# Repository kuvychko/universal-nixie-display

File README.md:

# universal-nixie-display

A programmable desktop display: six IN-14 Nixie tubes in a row, one A101 dekatron, a 2.8" ESP32
touchscreen and a rotary encoder, in a matte PLA enclosure on a tilt base. It is meant to be an
enjoyable object on its own (clock, timer, demo) and a numeric output device for a computer,
Raspberry Pi or experiment, driven over USB serial with a small SCPI-style command set.

**Companion site:** [kuvychko.github.io/universal-nixie-display](https://kuvychko.github.io/universal-nixie-display/)
· **Interactive explainer:** [How a dekatron counts](https://kuvychko.github.io/universal-nixie-display/how-it-works/dekatron/)

## The dekatron on the bench

The first tube to run is the A101, on a bench fixture: a printed housing for its socket, a shroud
over the tube, and a white clamshell around a perf board with a resistor divider and two step
buttons ([bench test](docs/bringup.md#optional-a101-bench-test)). It strikes, holds its glow and
steps reliably in both directions; the video shows it stepping from a 400 V supply.

*The bench fixture running from a 400 V supply (2026-10-20), and a still from the
[video](https://youtube.com/shorts/yVVf5zhSL-M) of the tube stepping (2026-10-19).*

The socket housing and shroud are not just for the bench: they go into the finished display as
they are, with the dekatron held horizontally, its end facing the viewer. The M3 inserts in the
housing's side faces are its mounting points in the enclosure. Print files and hardware are in
[enclosure/](enclosure/README.md#dekatron-bench-test-a101-bench-test-fixture).

## The dekatron on its own board

On 2026-10-25 the A101 ran from the first assembled controller/PSU board: the board's own HV
converter, bias supplies and guide drivers, with the RP2040 stepping the glow and counting its
passes over the index cathode. The video shows a demo loop: glow held still, slow rotation both
ways, speeding up to 200 steps/s, and a back-and-forth swing
([`tools/dekatron_demo.py`](tools/dekatron_demo.py), on the
[bring-up firmware](firmware/dekatron-bringup/README.md)). Stepping runs of up to 200 steps/s
in both directions counted every index pass exactly. With the tube lit the converter first held
only about 415 V of its 451 V setpoint; noise at the current-sense pin was ending its cycles
early. Since 2026-10-26, after three small reworks with kit parts, it regulates at the setpoint
with the tube lit ([assembly log](characterization/dekatron/2026-10-24_assembly_log.md)).

*The first controller/PSU board driving the A101
([video](https://youtu.be/51U_WKXrzoA), 2026-10-25).*

## Status

**Phase 1D and Phase 2 in parallel.** The dekatron controller/PSU board 1 is assembled: its rails,
HV converter and tube drive pass bring-up steps 1-3 (some measurements deferred), and the A101
steps and indexes on it under the [bring-up firmware](firmware/dekatron-bringup/README.md). Its
step-rate limits are measured: clean to 4000 steps/s, four times the datasheet rate, with counts
lost at 5000 ([logs](characterization/dekatron/2026-11-12_speed_sweep.md),
[2026-11-15](characterization/dekatron/2026-11-15_speed_sweep.md)). The
[dekatron controller firmware](firmware/dekatron/README.md) runs the tube over its USB
console, including the periodic index check and skip recovery
([log](characterization/dekatron/2026-11-14_index_check.md)), and ran an hour at its 2000 steps/s
limit, about 7.1 million steps, without a count error
([soak](characterization/dekatron/2026-11-15_overlap_soak.md)); its I2C path and the remaining
step 4-5 tests are next. The Nixie board is designed: schematics, PCB,
fab outputs and an [assembly checklist](hardware/nixie/assembly.md) are done; its parts were
ordered on 2026-11-10 and the board from PCBWay on 2026-11-11. The purchased Nixie HV module has
been measured on the bench ([log](characterization/nixie/2026-11-01_hv_module.md)). The planning
baseline is [docs/project_plan.md](docs/project_plan.md); design decisions and open items are in
[docs/hardware.md](docs/hardware.md), results in [docs/bringup.md](docs/bringup.md).

| Phase | Deliverable | State |
|---|---|---|
| 1A | Dekatron board architecture and power budget for 12 VDC input | Done |
| 1B | Hierarchical schematics and simulation evidence | Done (open simulation items in `docs/hardware.md`) |
| 1C | Dekatron controller/PSU PCB, BOM, fab files | Done: boards and parts received 2026-10-15/16 |
| 1D | Sectional bring-up and standalone firmware | **In progress:** board 1 hardware brought up (steps 1-3), step-rate limits measured (3a); controller firmware motion, index check and a one-hour soak tested with HV (step 4); I2C path and fault paths next |
| 2 | Nixie PSU qualification and six-tube controller/mount | **In progress:** HV module bench data and inrush; board designed; parts and boards ordered (2026-11-10/11) |
| 3 | ESP32 UI, encoder, I2C master, USB host commands | Not started |
| 4 | Enclosure | Started: A101 socket housing and shroud printed and in use |
| 5 | Rev A release | Not started |

### Dekatron controller/PSU at a glance

Readable without KiCad. Board as fabricated (commit f4fd414, ordered 2026-10-09); the schematic
title block still reads "Rev A draft". **Not yet fully validated:** bring-up is in progress
(Phase 1D); on board 1 the HV supply and tube drive run, the HV at its setpoint under load after
reworks to the current sense and switching frequency ([docs/bringup.md](docs/bringup.md)).

| What | File |
|---|---|
| Schematic (PDF, 4 sheets) | [hardware/dekatron/docs/dekatron-schematic.pdf](hardware/dekatron/docs/dekatron-schematic.pdf) |
| Board renders | [top](hardware/dekatron/docs/dekatron-pcb-top.png), [bottom](hardware/dekatron/docs/dekatron-pcb-bottom.png) |
| Bill of materials | [hardware/dekatron/bom.csv](hardware/dekatron/bom.csv) |
| Assembly checklist | [hardware/dekatron/assembly.md](hardware/dekatron/assembly.md) |
| Gerbers and drill files | [hardware/dekatron/fab/](hardware/dekatron/fab/README.md) |
| Bring-up results | [docs/bringup.md](docs/bringup.md) |

*Render and board 1 as assembled by hand (2026-10-27). The yellow disc capacitor beside U106 is a
bring-up rework: 470 pF at the converter's current-sense pin.*

### Nixie controller/mount at a glance

Six IN-14s, three HV5622 drivers and an RP2040 on one 164 x 53 mm board. Fabrication outputs
ordered from PCBWay 2026-11-11 (parts 2026-11-10); **not yet built**.

| What | File |
|---|---|
| Schematic (PDF, 3 sheets) | [hardware/nixie/docs/nixie-schematic.pdf](hardware/nixie/docs/nixie-schematic.pdf) |
| Board renders | [top](hardware/nixie/docs/nixie-pcb-top.png), [bottom](hardware/nixie/docs/nixie-pcb-bottom.png) |
| Bill of materials | [hardware/nixie/bom.csv](hardware/nixie/bom.csv) |
| Assembly checklist | [hardware/nixie/assembly.md](hardware/nixie/assembly.md) |
| Gerbers and drill files | [hardware/nixie/fab/](hardware/nixie/fab/README.md) |

## Architecture

```
 12 VDC adapter ──┬──────────────► purchased Nixie HV module (~170-180 V) ──► Nixie controller/mount
                  │                                                           (6× IN-14, 3× HV5622, RP2040-Zero)
                  └──► dekatron controller/PSU ──► A101 (HV, bias, guide drive, index sense, RP2040-Zero)
                         │ 5 V buck out
                         ▼
                   ESP32 2.8" display board ◄── USB-C to host (SCPI-style serial)
                   (UI, encoder, presets, I2C master)
                         │ I2C, 3.3 V
                         └──► dekatron controller, Nixie controller
```

The ESP32 owns *what* is displayed; the RP2040 controllers own time-sensitive sequences and
hardware state. See [docs/architecture.md](docs/architecture.md).

## Documentation

| Document | Contents |
|---|---|
| [docs/project_plan.md](docs/project_plan.md) | Planning baseline: scope, decisions, phases and acceptance gates |
| [docs/architecture.md](docs/architecture.md) | Power distribution, board boundaries, ownership |
| [docs/hardware.md](docs/hardware.md) | Electrical design, open decisions, harness tables |
| [docs/i2c_protocol.md](docs/i2c_protocol.md) | Versioned controller command/status contracts |
| [docs/host_interface.md](docs/host_interface.md) | USB serial / SCPI-style host contract |
| [docs/bringup.md](docs/bringup.md) | Module bring-up procedures and acceptance results |
| [docs/development.md](docs/development.md) | Toolchains, KiCad workflow, generated-file policy |
| [docs/references.md](docs/references.md) | Datasheets, source designs, attribution and reuse terms |
| [docs/companion_site.md](docs/companion_site.md) | Plan for the companion website (`website/`); the published site is [here](https://kuvychko.github.io/universal-nixie-display/) |

## Repository layout

| Path | Contents |
|---|---|
| `hardware/dekatron/` | Dekatron controller/PSU KiCad project; `simulation/` holds supply and drive/sense models |
| `hardware/nixie/` | Nixie controller/mount KiCad project (boards ordered 2026-11-11) |
| `hardware/power/` | Purchased Nixie PSU specification and system power harness (planned, Phase 2) |
| `hardware/lib/` | Shared symbols and footprints (planned; the dekatron board's own library is in `hardware/dekatron/lib/`) |
| `firmware/display/` | ESP32 main application, PlatformIO (planned, Phase 3) |
| `firmware/dekatron/` | RP2040 dekatron controller and standalone diagnostics: [spec and build](firmware/dekatron/README.md), v0.1 (Phase 1D) |
| `firmware/dekatron-bringup/` | Dekatron board bring-up firmware: HV enable, guide drive, status over USB serial |
| `firmware/nixie/` | RP2040 Nixie controller (planned, Phase 2) |
| `firmware/common/` | Shared protocol definitions: [`dekatron_protocol.h`](firmware/common/dekatron_protocol.h) |
| `enclosure/` | Printed parts, one folder per assembly (SOLIDWORKS source, STEP, 3MF); index and print settings in its README |
| `tools/` | KiCad generators (schematic, placement, routing, silkscreen) and the site checker; dekatron bring-up and demo scripts (`hv_bringup.py`, `dekatron_demo.py`), scope photo tool |
| `characterization/` | Dated measurements: dekatron board 1 assembly log, Nixie HV module bench log |
| `tests/` | Host protocol/formatting tests, hardware test scripts (planned) |
| `website/` | Companion site source (MkDocs Material; `mkdocs.yml` at the root) |

## Safety: read this first

> [!WARNING]
> **This project uses dangerous voltages.** The dekatron runs from about 450 V DC and the Nixies
> from about 170-180 V DC. A shock at these voltages can cause serious injury or death, and
> capacitors can hold a charge after the power is off. If you build, test or copy anything here,
> you do so **entirely at your own risk**. Work on it only if you understand high-voltage
> circuits and know what you are doing. The designs and documents are provided as is, without
> warranty of any kind (see [LICENSE](LICENSE)).

The **A101 bench test** ([docs/bringup.md](docs/bringup.md#optional-a101-bench-test);
[video](https://youtube.com/shorts/yVVf5zhSL-M)) is the most
exposed part of the project: open wiring on a perf board, the anode at up to 450 V and every other
wire at 50-106 V, none of them at ground. If you try it:

* **One hand.** While anything is powered, keep one hand away from the circuit, for example in a
  pocket. Operate buttons by their insulated caps.
* **Limit the current.** Use a bench supply with an adjustable current limit, set to a few
  milliamps (2-3 mA for the bench test).
* **Power off to touch.** Make and change connections only with the supply off and its output
  discharged; measure before you touch anything.
* **Rated equipment.** Use meters, probes and leads rated for the voltage. Clip leads on before
  powering up rather than holding probes on live nodes.
* **Not alone, not tired.** Work with someone nearby, and stop when you are not concentrating.

On the boards, discharge paths, clearances and probe ratings are design requirements, not
afterthoughts (project plan §4). Printed plastic parts keep fingers away; they are not
high-voltage insulation.

## Acknowledgements

The dekatron controller/PSU boards were made by [PCBWay](https://www.pcbway.com/), who
sponsored their fabrication. Ordering was easy and smooth: upload the Gerber zip from
[`hardware/dekatron/fab/`](hardware/dekatron/fab/), pick the options and go. What stands out is
how much information their website gives, from exactly what you are ordering to where your order
is in production. There is even a full walk-through of how a board is made, step by step:
[PCB manufacturing process](https://www.pcbway.com/pcb-service.html). Beyond bare boards they
also make SMD stencils and offer assembly, CNC machining and 3D printing.

The Gerbers went up on the evening of 2026-10-08 and the five boards were on the bench on
2026-10-15. They came sealed in bubble wrap with a silica-gel desiccant pack, and the label lists
the order, the uploaded file, size, layer count, thickness and quantity. The edges are milled
clean: no break-away tab remnants to file, so the boards were ready to use straight out of the bag.

PCBWay is sponsoring the Nixie controller/mount boards too: ordered on 2026-11-11 from
[`hardware/nixie/fab/`](hardware/nixie/fab/), in fabrication as of 2026-11-14.

Thank you, PCBWay, for supporting an open-source hardware project!

## Licence

Hardware, enclosure, documentation and the companion site's content: CERN-OHL-P v2. Firmware,
tools, tests and the site's JavaScript: MIT. See [LICENSE](LICENSE).

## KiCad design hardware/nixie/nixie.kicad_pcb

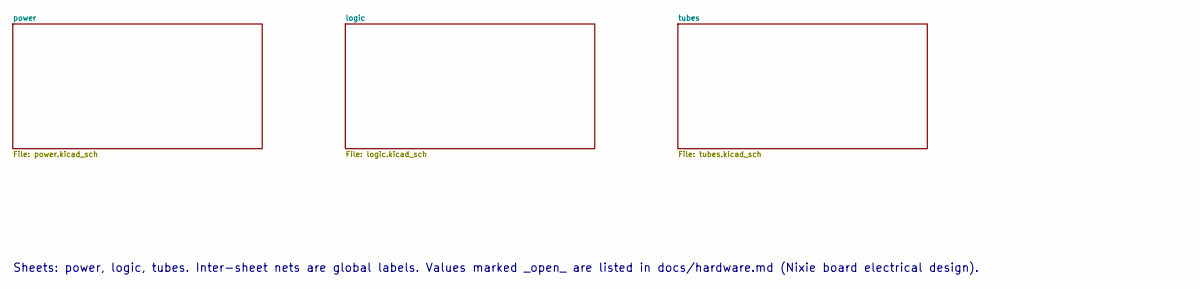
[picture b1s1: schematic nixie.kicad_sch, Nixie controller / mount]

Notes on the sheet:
Sheets: power, logic, tubes. Inter-sheet nets are global labels. Values marked _open_ are listed in docs/hardware.md (Nixie board electrical design).

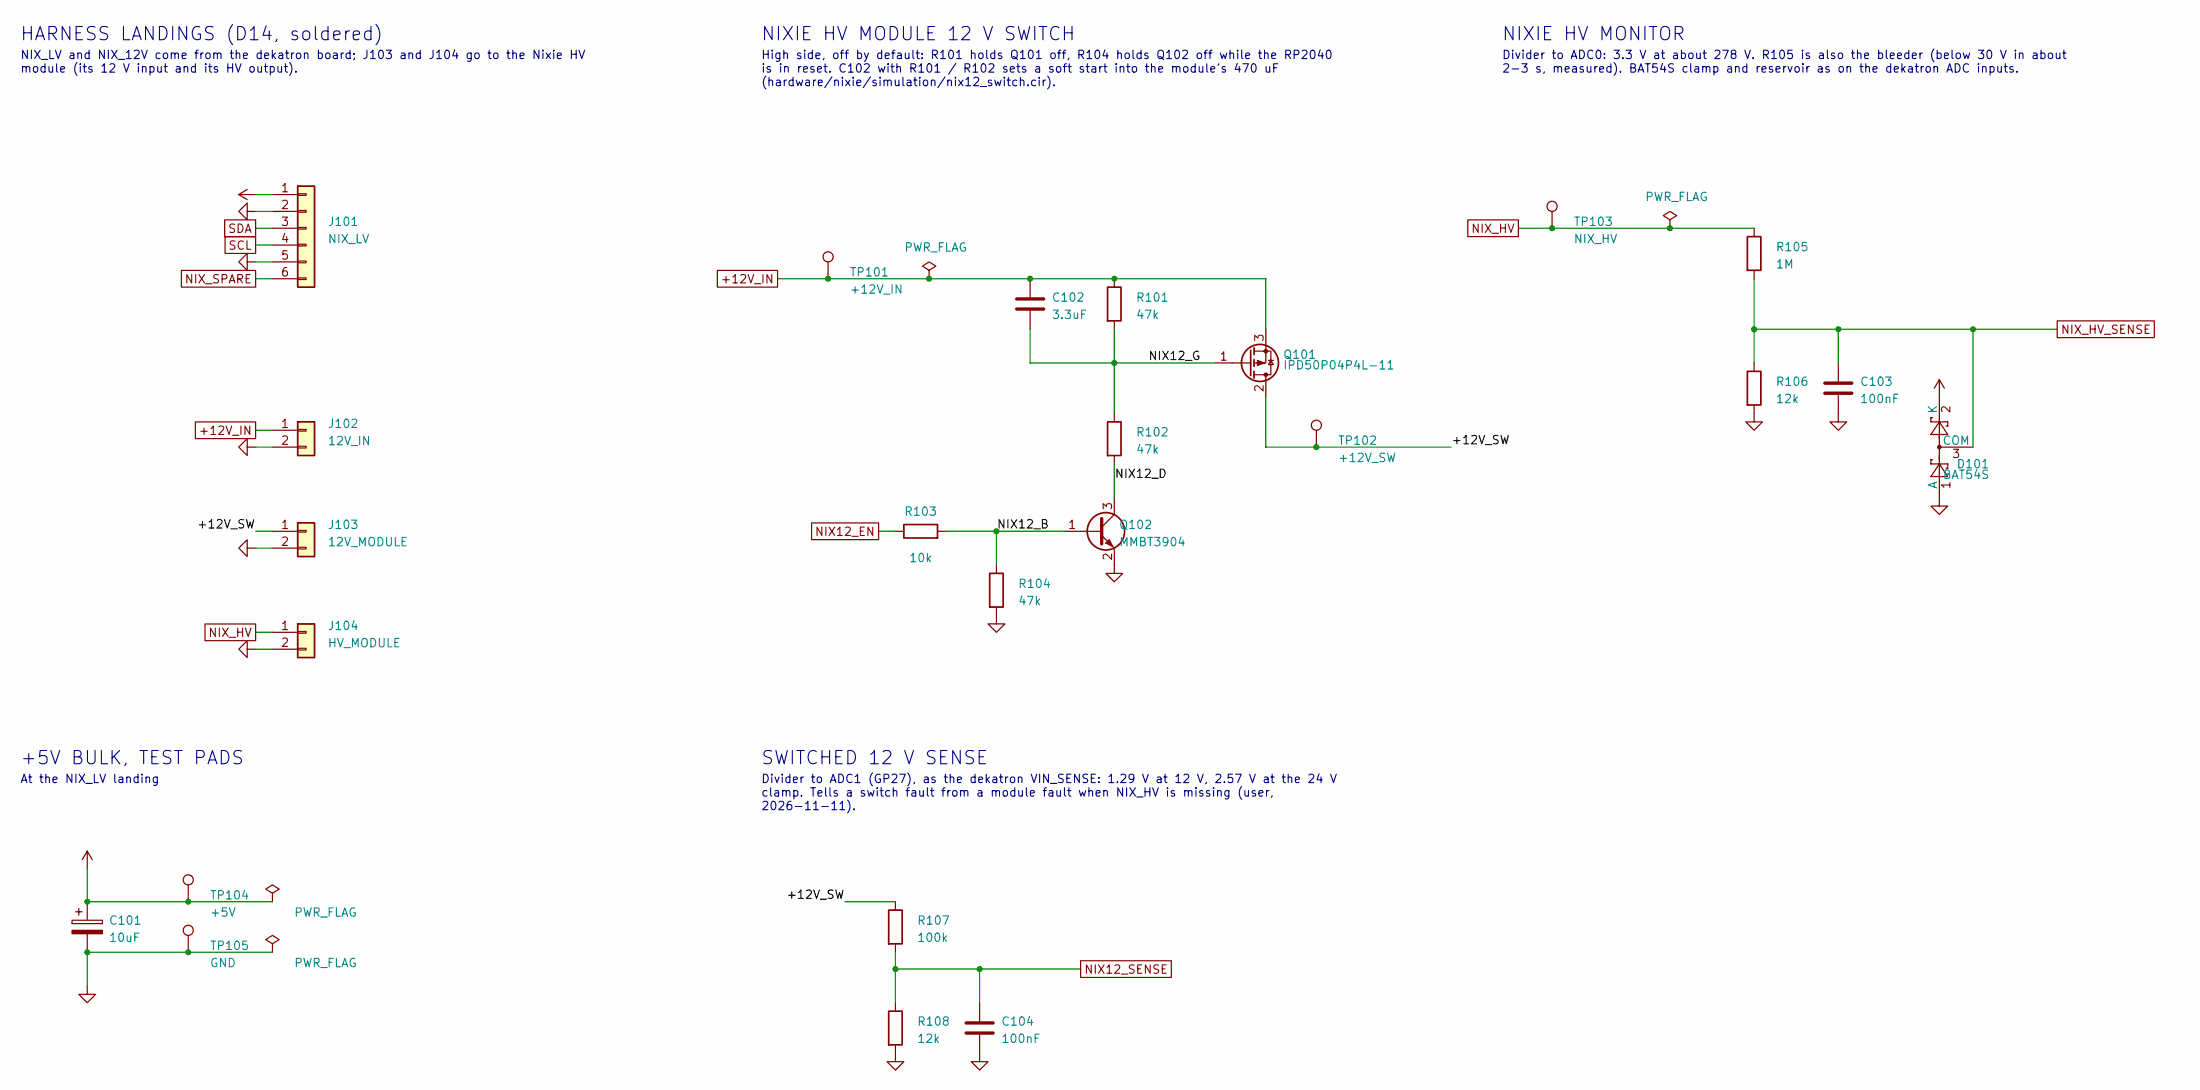
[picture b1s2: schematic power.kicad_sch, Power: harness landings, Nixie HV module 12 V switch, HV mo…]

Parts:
C101: 10uF; CP_EIA-3216-18_Kemet-A; Rating 16 V tantalum; MPN F911C106MAAAJ6
C102: 3.3uF; C_1206_3216Metric; Rating 25 V X7R
C103, C104: 100nF; C_1206_3216Metric; Rating 50 V X7R; MPN CC1206JPX7R9BB104
D101: BAT54S; SOT-23; Rating 30 V Schottky pair; MPN BAT54S RFG
J101: NIX_LV; SolderWire-0.5sqmm_1x06_P4.8mm_D0.9mm_OD2.3mm
J102: 12V_IN; SolderWire-0.5sqmm_1x02_P4.8mm_D0.9mm_OD2.3mm
J103: 12V_MODULE; SolderWire-0.5sqmm_1x02_P4.8mm_D0.9mm_OD2.3mm
J104: HV_MODULE; SolderWire-0.5sqmm_1x02_P4.8mm_D0.9mm_OD2.3mm
Q101: IPD50P04P4L-11; TO-252-2; Rating -40 V, 17.2 mohm max at VGS -4.5 V, VGS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; MPN IPD50P04P4L11ATMA2
Q102: MMBT3904; SOT-23; Rating 40 V NPN; MPN MMBT3904
R101, R102, R104: 47k; R_1206_3216Metric
R103: 10k; R_1206_3216Metric
R105: 1M; R_Axial_DIN0411_L9.9mm_D3.6mm_P15.24mm_Horizontal; Rating HHV-50: 0.5 W; MPN HHV-50FT-52-1M
R106: 12k; R_1206_3216Metric; Rating 1 %; MPN ERJ-8ENF1202V
R107: 100k; R_1206_3216Metric
R108: 12k; R_1206_3216Metric; Rating 1 %
TP101: +12V_IN; TestPoint_THTPad_D1.5mm_Drill0.7mm
TP102: +12V_SW; TestPoint_THTPad_D1.5mm_Drill0.7mm
TP103: NIX_HV; TestPoint_THTPad_D1.5mm_Drill0.7mm
TP104: +5V; TestPoint_THTPad_D1.5mm_Drill0.7mm
TP105: GND; TestPoint_THTPad_D1.5mm_Drill0.7mm

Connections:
+3V3: D101.2 (K); also elsewhere on the board
+5V: C101.1, J101.1, TP104.1; also elsewhere on the board
+12V_IN: C102.1, J102.1, Q101.3 (S), R101.1, TP101.1; also elsewhere on the board
/power/+12V_SW: J103.1, Q101.2 (D), R107.1, TP102.1
/power/NIX12_B: Q102.1 (B), R103.2, R104.1
/power/NIX12_D: Q102.3 (C), R102.2
/power/NIX12_G: C102.2, Q101.1 (G), R101.2, R102.1
GND: C101.2, C103.2, C104.2, D101.1 (A), J101.2, J101.5, J102.2, J103.2, J104.2, Q102.2 (E), R104.2, R106.2, R108.2, TP105.1; also elsewhere on the board
NIX12_EN: R103.1; also elsewhere on the board
NIX12_SENSE: C104.1, R107.2, R108.1; also elsewhere on the board
NIX_HV: J104.1, R105.1, TP103.1; also elsewhere on the board
NIX_HV_SENSE: C103.1, D101.3 (COM), R105.2, R106.1; also elsewhere on the board
NIX_SPARE: J101.6; also elsewhere on the board
SCL: J101.4; also elsewhere on the board
SDA: J101.3; also elsewhere on the board

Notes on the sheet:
HARNESS LANDINGS (D14, soldered)
NIX_LV and NIX_12V come from the dekatron board; J103 and J104 go to the Nixie HV module (its 12 V input and its HV output).
+5V BULK, TEST PADS
At the NIX_LV landing
NIXIE HV MODULE 12 V SWITCH
High side, off by default: R101 holds Q101 off, R104 holds Q102 off while the RP2040 is in reset. C102 with R101 / R102 sets a soft start into the module's 470 uF (hardware/nixie/simulation/nix12_switch.cir).
SWITCHED 12 V SENSE
Divider to ADC1 (GP27), as the dekatron VIN_SENSE: 1.29 V at 12 V, 2.57 V at the 24 V clamp. Tells a switch fault from a module fault when NIX_HV is missing (user, 2026-11-11).
NIXIE HV MONITOR
Divider to ADC0: 3.3 V at about 278 V. R105 is also the bleeder (below 30 V in about 2-3 s, measured). BAT54S clamp and reservoir as on the dekatron ADC inputs.

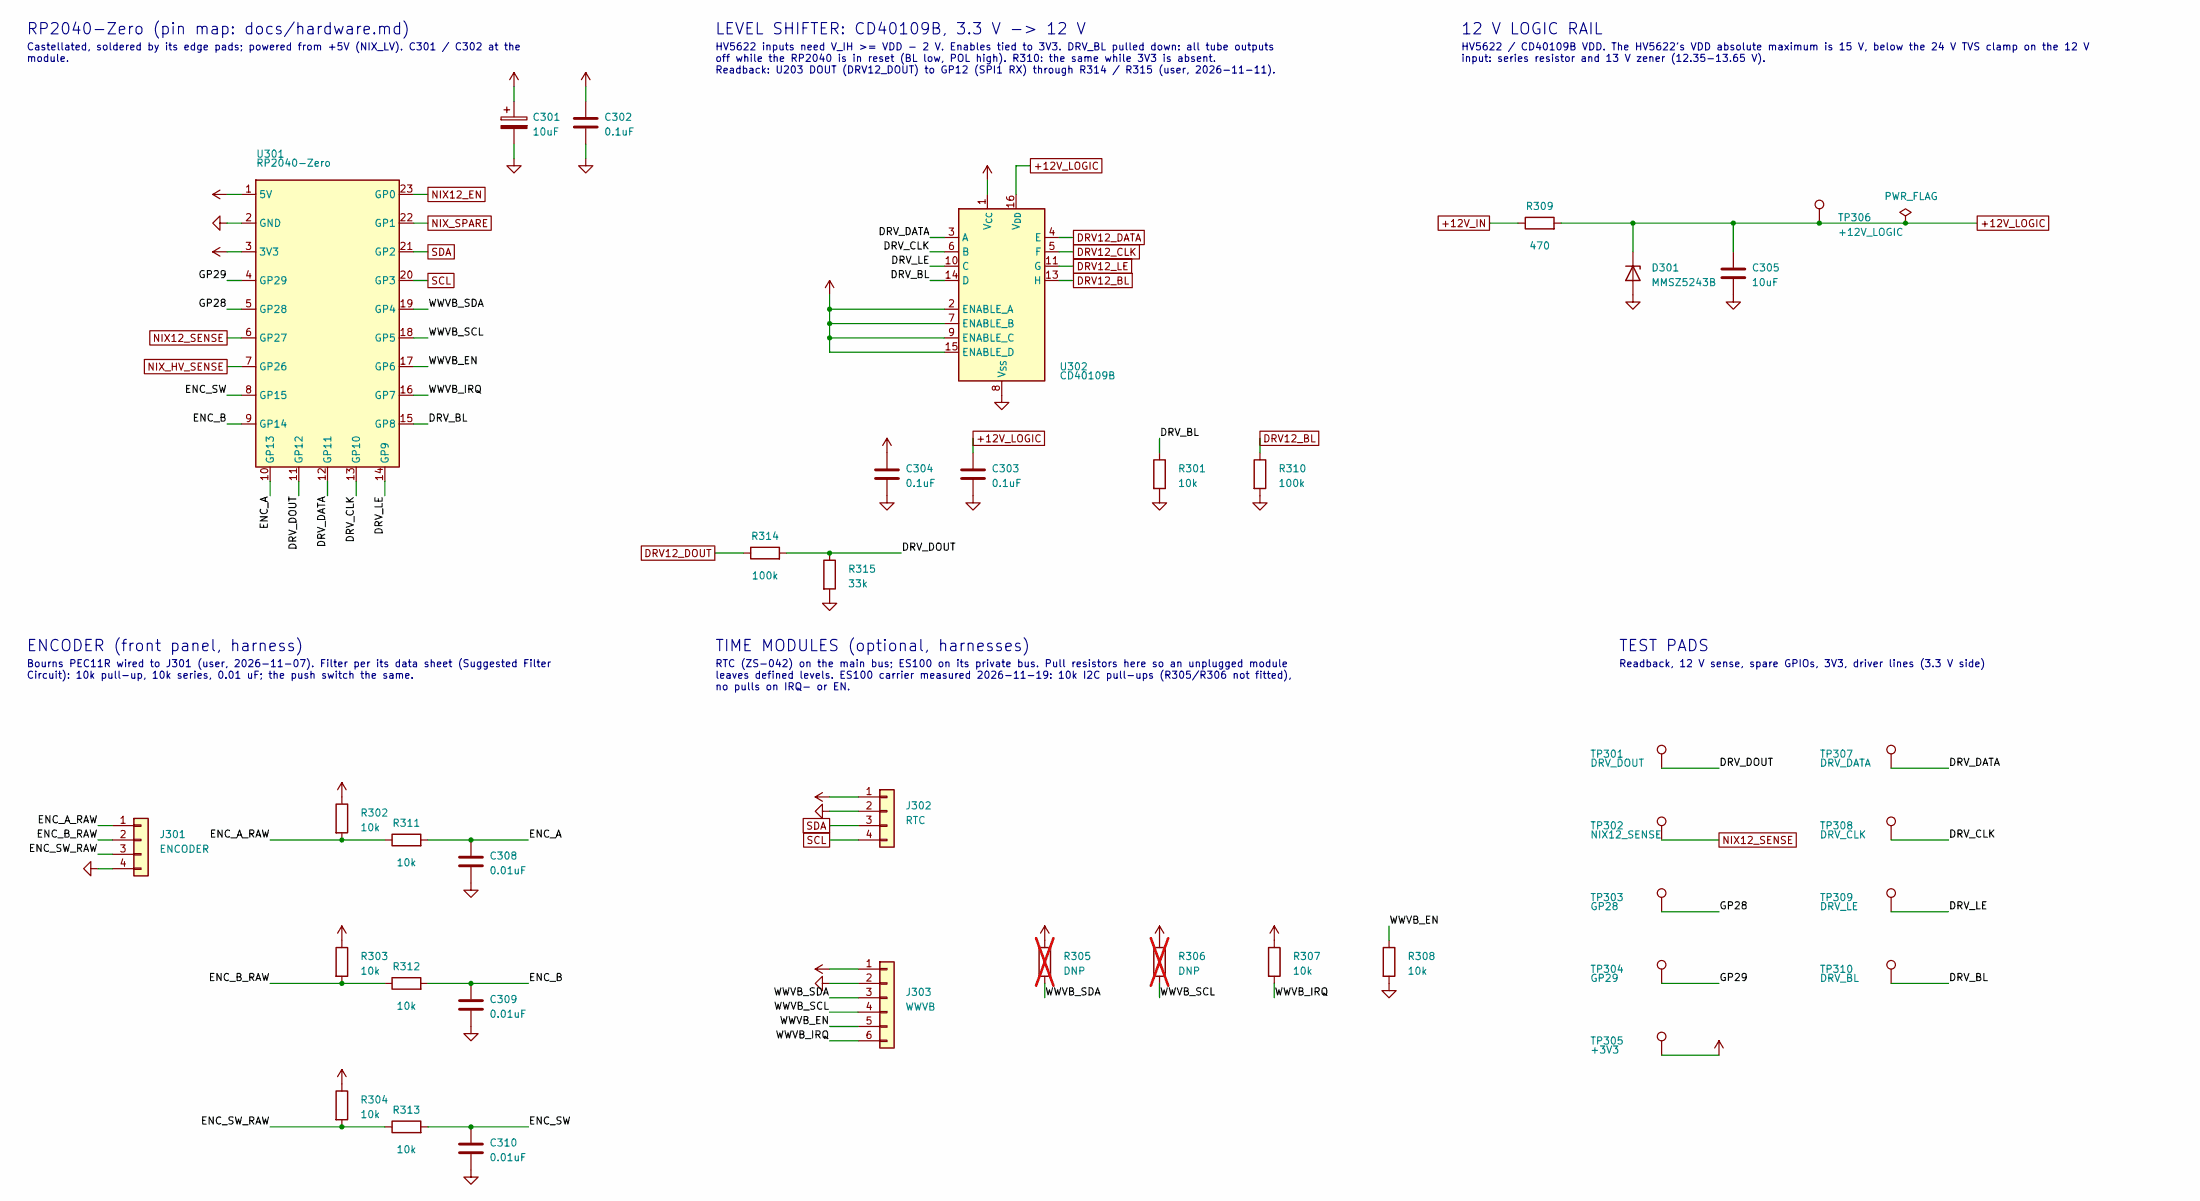
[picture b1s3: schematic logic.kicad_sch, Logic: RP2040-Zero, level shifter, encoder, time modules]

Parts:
C301: 10uF; CP_EIA-3216-18_Kemet-A; Rating 16 V tantalum; MPN F911C106MAAAJ6
C302, C303, C304: 0.1uF; C_1206_3216Metric; Rating 50 V X7R; MPN CC1206JPX7R9BB104
C305: 10uF; C_1206_3216Metric; Rating 25 V X7R
C308, C309, C310: 0.01uF; C_1206_3216Metric; Rating 25 V X7R; MPN 12063C103JAT2A
D301: MMSZ5243B; D_SOD-123; Rating 13 V, 500 mW, SOD-123; MPN MMSZ5243B
J301: ENCODER; SolderWire-0.5sqmm_1x04_P4.8mm_D0.9mm_OD2.3mm
J302: RTC; SolderWire-0.5sqmm_1x04_P4.8mm_D0.9mm_OD2.3mm
J303: WWVB; SolderWire-0.5sqmm_1x06_P4.8mm_D0.9mm_OD2.3mm
R301, R302, R303, R304, R307, R308, R311, R312, R313: 10k; R_1206_3216Metric
R305, R306: DNP; R_1206_3216Metric; not fitted
R309: 470; R_1206_3216Metric; Rating 1206, 0.25 W
R310, R314: 100k; R_1206_3216Metric
R315: 33k; R_1206_3216Metric
TP301: DRV_DOUT; TestPoint_THTPad_D1.5mm_Drill0.7mm
TP302: NIX12_SENSE; TestPoint_THTPad_D1.5mm_Drill0.7mm
TP303: GP28; TestPoint_THTPad_D1.5mm_Drill0.7mm
TP304: GP29; TestPoint_THTPad_D1.5mm_Drill0.7mm
TP305: +3V3; TestPoint_THTPad_D1.5mm_Drill0.7mm
TP306: +12V_LOGIC; TestPoint_THTPad_D1.5mm_Drill0.7mm
TP307: DRV_DATA; TestPoint_THTPad_D1.5mm_Drill0.7mm
TP308: DRV_CLK; TestPoint_THTPad_D1.5mm_Drill0.7mm
TP309: DRV_LE; TestPoint_THTPad_D1.5mm_Drill0.7mm
TP310: DRV_BL; TestPoint_THTPad_D1.5mm_Drill0.7mm
U301: RP2040-Zero; RP2040-Zero_Castellated; Rating headerless, castellated; MPN RP2040-Zero
U302: CD40109B; SO-16_5.3x10.2mm_P1.27mm; Rating VCC/VDD 3-18 V, SOP-16 (NS) 5.3 mm; MPN CD40109BNSRE4

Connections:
+3V3: C302.1, C304.1, J302.1, J303.1, R302.1, R303.1, R304.1, R305.1, R306.1, R307.1, TP305.1, U301.3 (3V3), U302.1 (V_{CC}), U302.2 (ENABLE_A), U302.7 (ENABLE_B), U302.9 (ENABLE_C), U302.15 (ENABLE_D); also elsewhere on the board
+5V: C301.1, U301.1 (5V); also elsewhere on the board
+12V_IN: R309.1; also elsewhere on the board
+12V_LOGIC: C303.1, C305.1, D301.1 (K), R309.2, TP306.1, U302.16 (V_{DD}); also elsewhere on the board
/logic/DRV_BL: R301.1, TP310.1, U301.15 (GP8), U302.14 (D)
/logic/DRV_CLK: TP308.1, U301.13 (GP10), U302.6 (B)
/logic/DRV_DATA: TP307.1, U301.12 (GP11), U302.3 (A)
/logic/DRV_DOUT: R314.2, R315.1, TP301.1, U301.11 (GP12)
/logic/DRV_LE: TP309.1, U301.14 (GP9), U302.10 (C)
/logic/ENC_A: C308.1, R311.2, U301.10 (GP13)
/logic/ENC_A_RAW: J301.1, R302.2, R311.1
/logic/ENC_B: C309.1, R312.2, U301.9 (GP14)
/logic/ENC_B_RAW: J301.2, R303.2, R312.1
/logic/ENC_SW: C310.1, R313.2, U301.8 (GP15)
/logic/ENC_SW_RAW: J301.3, R304.2, R313.1
/logic/GP28: TP303.1, U301.5 (GP28)
/logic/GP29: TP304.1, U301.4 (GP29)
/logic/WWVB_EN: J303.5, R308.1, U301.17 (GP6)
/logic/WWVB_IRQ: J303.6, R307.2, U301.16 (GP7)
/logic/WWVB_SCL: J303.4, R306.2, U301.18 (GP5)
/logic/WWVB_SDA: J303.3, R305.2, U301.19 (GP4)
DRV12_BL: R310.1, U302.13 (H); also elsewhere on the board
DRV12_CLK: U302.5 (F); also elsewhere on the board
DRV12_DATA: U302.4 (E); also elsewhere on the board
DRV12_DOUT: R314.1; also elsewhere on the board
DRV12_LE: U302.11 (G); also elsewhere on the board
GND: C301.2, C302.2, C303.2, C304.2, C305.2, C308.2, C309.2, C310.2, D301.2 (A), J301.4, J302.2, J303.2, R301.2, R308.2, R310.2, R315.2, U301.2 (GND), U302.8 (V_{SS}); also elsewhere on the board
NIX12_EN: U301.23 (GP0); also elsewhere on the board
NIX12_SENSE: TP302.1, U301.6 (GP27); also elsewhere on the board
NIX_HV_SENSE: U301.7 (GP26); also elsewhere on the board
NIX_SPARE: U301.22 (GP1); also elsewhere on the board
SCL: J302.4, U301.20 (GP3); also elsewhere on the board
SDA: J302.3, U301.21 (GP2); also elsewhere on the board

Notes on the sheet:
RP2040-Zero (pin map: docs/hardware.md)
Castellated, soldered by its edge pads; powered from +5V (NIX_LV). C301 / C302 at the module.
LEVEL SHIFTER: CD40109B, 3.3 V -> 12 V
HV5622 inputs need V_IH >= VDD - 2 V. Enables tied to 3V3. DRV_BL pulled down: all tube outputs off while the RP2040 is in reset (BL low, POL high). R310: the same while 3V3 is absent. Readback: U203 DOUT (DRV12_DOUT) to GP12 (SPI1 RX) through R314 / R315 (user, 2026-11-11).
12 V LOGIC RAIL
HV5622 / CD40109B VDD. The HV5622's VDD absolute maximum is 15 V, below the 24 V TVS clamp on the 12 V input: series resistor and 13 V zener (12.35-13.65 V).
ENCODER (front panel, harness)
Bourns PEC11R wired to J301 (user, 2026-11-07). Filter per its data sheet (Suggested Filter Circuit): 10k pull-up, 10k series, 0.01 uF; the push switch the same.
TIME MODULES (optional, harnesses)
RTC (ZS-042) on the main bus; ES100 on its private bus. Pull resistors here so an unplugged module leaves defined levels. ES100 carrier measured 2026-11-19: 10k I2C pull-ups (R305/R306 not fitted), no pulls on IRQ- or EN.
TEST PADS
Readback, 12 V sense, spare GPIOs, 3V3, driver lines (3.3 V side)

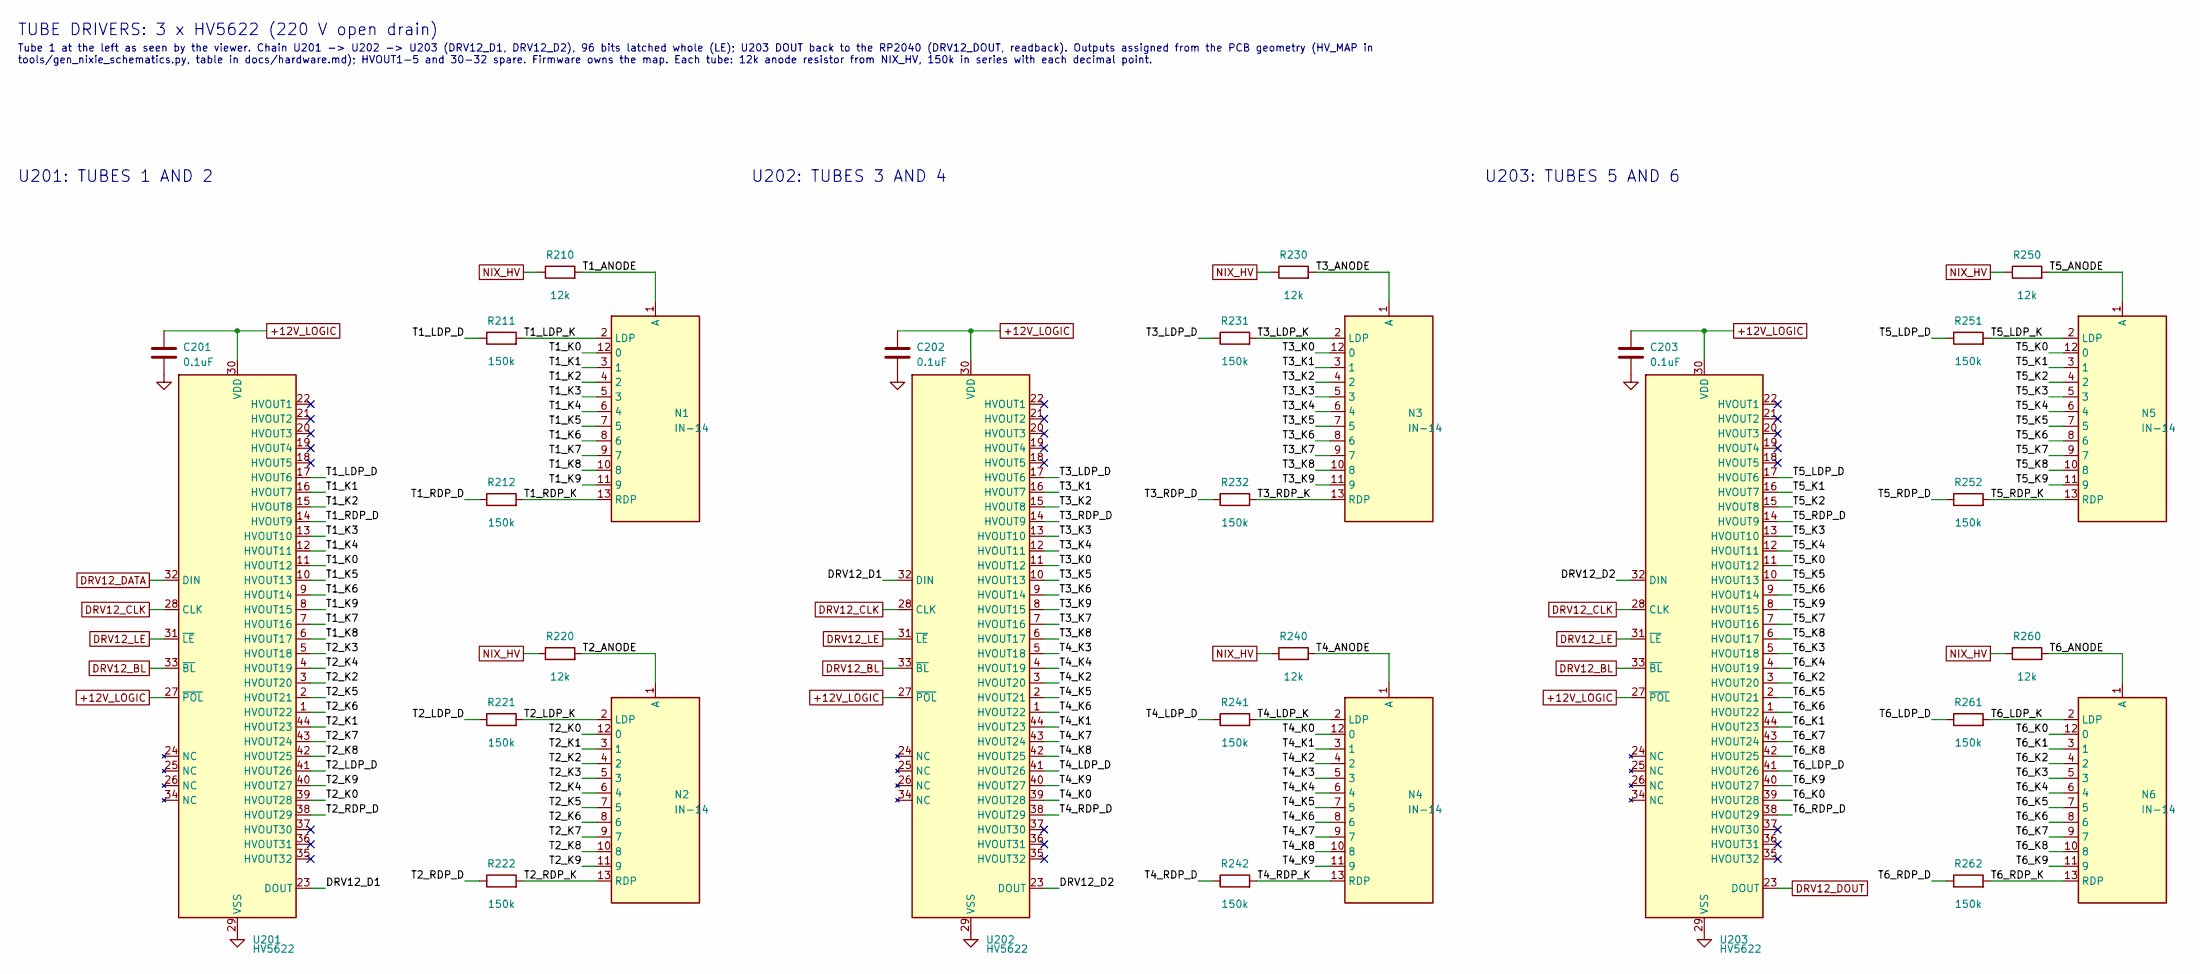
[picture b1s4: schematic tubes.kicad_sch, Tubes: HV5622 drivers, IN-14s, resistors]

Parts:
C201, C202, C203: 0.1uF; C_1206_3216Metric; Rating 50 V X7R; MPN CC1206JPX7R9BB104
N1, N2, N3, N4, N5, N6: IN-14; MPN IN-14
R210, R220, R230, R240, R250, R260: 12k; R_Axial_DIN0207_L6.3mm_D2.5mm_P10.16mm_Horizontal; Rating MRS25: 0.6 W, 350 V, 1 %, 50 ppm/K; MPN MRS25000C1202FRP00
R211, R212, R221, R222, R231, R232, R241, R242, R251, R252, R261, R262: 150k; R_1206_3216Metric
U201, U202, U203: HV5622; Microchip_PQFP-44_10x10mm_P0.8mm; Rating 220 V outputs, PQFP-44 0.8 mm; MPN HV5622PG-G

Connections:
+12V_LOGIC: C201.1, C202.1, C203.1, U201.27 (~POL), U201.30 (VDD), U202.27 (~POL), U202.30 (VDD), U203.27 (~POL), U203.30 (VDD); also elsewhere on the board
/tubes/DRV12_D1: U201.23 (DOUT), U202.32 (DIN)
/tubes/DRV12_D2: U202.23 (DOUT), U203.32 (DIN)
/tubes/T1_ANODE: N1.1 (A), R210.2
/tubes/T1_K0: N1.12 (0), U201.11 (HVOUT12)
/tubes/T1_K1: N1.3 (1), U201.16 (HVOUT7)
/tubes/T1_K2: N1.4 (2), U201.15 (HVOUT8)
/tubes/T1_K3: N1.5 (3), U201.13 (HVOUT10)
/tubes/T1_K4: N1.6 (4), U201.12 (HVOUT11)
/tubes/T1_K5: N1.7 (5), U201.10 (HVOUT13)
/tubes/T1_K6: N1.8 (6), U201.9 (HVOUT14)
/tubes/T1_K7: N1.9 (7), U201.7 (HVOUT16)
/tubes/T1_K8: N1.10 (8), U201.6 (HVOUT17)
/tubes/T1_K9: N1.11 (9), U201.8 (HVOUT15)
/tubes/T1_LDP_D: R211.1, U201.17 (HVOUT6)
/tubes/T1_LDP_K: N1.2 (LDP), R211.2
/tubes/T1_RDP_D: R212.1, U201.14 (HVOUT9)
/tubes/T1_RDP_K: N1.13 (RDP), R212.2
/tubes/T2_ANODE: N2.1 (A), R220.2
/tubes/T2_K0: N2.12 (0), U201.39 (HVOUT28)
/tubes/T2_K1: N2.3 (1), U201.44 (HVOUT23)
/tubes/T2_K2: N2.4 (2), U201.3 (HVOUT20)
/tubes/T2_K3: N2.5 (3), U201.5 (HVOUT18)
/tubes/T2_K4: N2.6 (4), U201.4 (HVOUT19)
/tubes/T2_K5: N2.7 (5), U201.2 (HVOUT21)
/tubes/T2_K6: N2.8 (6), U201.1 (HVOUT22)
/tubes/T2_K7: N2.9 (7), U201.43 (HVOUT24)
/tubes/T2_K8: N2.10 (8), U201.42 (HVOUT25)
/tubes/T2_K9: N2.11 (9), U201.40 (HVOUT27)
/tubes/T2_LDP_D: R221.1, U201.41 (HVOUT26)
/tubes/T2_LDP_K: N2.2 (LDP), R221.2
/tubes/T2_RDP_D: R222.1, U201.38 (HVOUT29)
/tubes/T2_RDP_K: N2.13 (RDP), R222.2
/tubes/T3_ANODE: N3.1 (A), R230.2
/tubes/T3_K0: N3.12 (0), U202.11 (HVOUT12)
/tubes/T3_K1: N3.3 (1), U202.16 (HVOUT7)
/tubes/T3_K2: N3.4 (2), U202.15 (HVOUT8)
/tubes/T3_K3: N3.5 (3), U202.13 (HVOUT10)
/tubes/T3_K4: N3.6 (4), U202.12 (HVOUT11)
/tubes/T3_K5: N3.7 (5), U202.10 (HVOUT13)
/tubes/T3_K6: N3.8 (6), U202.9 (HVOUT14)
/tubes/T3_K7: N3.9 (7), U202.7 (HVOUT16)
/tubes/T3_K8: N3.10 (8), U202.6 (HVOUT17)
/tubes/T3_K9: N3.11 (9), U202.8 (HVOUT15)
/tubes/T3_LDP_D: R231.1, U202.17 (HVOUT6)
/tubes/T3_LDP_K: N3.2 (LDP), R231.2
/tubes/T3_RDP_D: R232.1, U202.14 (HVOUT9)
/tubes/T3_RDP_K: N3.13 (RDP), R232.2
/tubes/T4_ANODE: N4.1 (A), R240.2
/tubes/T4_K0: N4.12 (0), U202.39 (HVOUT28)
/tubes/T4_K1: N4.3 (1), U202.44 (HVOUT23)
/tubes/T4_K2: N4.4 (2), U202.3 (HVOUT20)
/tubes/T4_K3: N4.5 (3), U202.5 (HVOUT18)
/tubes/T4_K4: N4.6 (4), U202.4 (HVOUT19)
/tubes/T4_K5: N4.7 (5), U202.2 (HVOUT21)
/tubes/T4_K6: N4.8 (6), U202.1 (HVOUT22)
/tubes/T4_K7: N4.9 (7), U202.43 (HVOUT24)
/tubes/T4_K8: N4.10 (8), U202.42 (HVOUT25)
/tubes/T4_K9: N4.11 (9), U202.40 (HVOUT27)
/tubes/T4_LDP_D: R241.1, U202.41 (HVOUT26)
/tubes/T4_LDP_K: N4.2 (LDP), R241.2
/tubes/T4_RDP_D: R242.1, U202.38 (HVOUT29)
/tubes/T4_RDP_K: N4.13 (RDP), R242.2
/tubes/T5_ANODE: N5.1 (A), R250.2
/tubes/T5_K0: N5.12 (0), U203.11 (HVOUT12)
/tubes/T5_K1: N5.3 (1), U203.16 (HVOUT7)
/tubes/T5_K2: N5.4 (2), U203.15 (HVOUT8)
/tubes/T5_K3: N5.5 (3), U203.13 (HVOUT10)
/tubes/T5_K4: N5.6 (4), U203.12 (HVOUT11)
/tubes/T5_K5: N5.7 (5), U203.10 (HVOUT13)
/tubes/T5_K6: N5.8 (6), U203.9 (HVOUT14)
/tubes/T5_K7: N5.9 (7), U203.7 (HVOUT16)
/tubes/T5_K8: N5.10 (8), U203.6 (HVOUT17)
/tubes/T5_K9: N5.11 (9), U203.8 (HVOUT15)
/tubes/T5_LDP_D: R251.1, U203.17 (HVOUT6)
/tubes/T5_LDP_K: N5.2 (LDP), R251.2
/tubes/T5_RDP_D: R252.1, U203.14 (HVOUT9)
/tubes/T5_RDP_K: N5.13 (RDP), R252.2
/tubes/T6_ANODE: N6.1 (A), R260.2
/tubes/T6_K0: N6.12 (0), U203.39 (HVOUT28)
/tubes/T6_K1: N6.3 (1), U203.44 (HVOUT23)
/tubes/T6_K2: N6.4 (2), U203.3 (HVOUT20)
/tubes/T6_K3: N6.5 (3), U203.5 (HVOUT18)
/tubes/T6_K4: N6.6 (4), U203.4 (HVOUT19)
/tubes/T6_K5: N6.7 (5), U203.2 (HVOUT21)
/tubes/T6_K6: N6.8 (6), U203.1 (HVOUT22)
/tubes/T6_K7: N6.9 (7), U203.43 (HVOUT24)
/tubes/T6_K8: N6.10 (8), U203.42 (HVOUT25)
/tubes/T6_K9: N6.11 (9), U203.40 (HVOUT27)
/tubes/T6_LDP_D: R261.1, U203.41 (HVOUT26)
/tubes/T6_LDP_K: N6.2 (LDP), R261.2
/tubes/T6_RDP_D: R262.1, U203.38 (HVOUT29)
/tubes/T6_RDP_K: N6.13 (RDP), R262.2
DRV12_BL: U201.33 (~BL), U202.33 (~BL), U203.33 (~BL); also elsewhere on the board
DRV12_CLK: U201.28 (CLK), U202.28 (CLK), U203.28 (CLK); also elsewhere on the board
DRV12_DATA: U201.32 (DIN); also elsewhere on the board
DRV12_DOUT: U203.23 (DOUT); also elsewhere on the board
DRV12_LE: U201.31 (~LE), U202.31 (~LE), U203.31 (~LE); also elsewhere on the board
GND: C201.2, C202.2, C203.2, U201.29 (VSS), U202.29 (VSS), U203.29 (VSS); also elsewhere on the board
NIX_HV: R210.1, R220.1, R230.1, R240.1, R250.1, R260.1; also elsewhere on the board

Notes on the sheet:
TUBE DRIVERS: 3 x HV5622 (220 V open drain)
Tube 1 at the left as seen by the viewer. Chain U201 -> U202 -> U203 (DRV12_D1, DRV12_D2), 96 bits latched whole (LE); U203 DOUT back to the RP2040 (DRV12_DOUT, readback). Outputs assigned from the PCB geometry (HV_MAP in tools/gen_nixie_schematics.py, table in docs/hardware.md); HVOUT1-5 and 30-32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
U201: TUBES 1 AND 2
U202: TUBES 3 AND 4
U203: TUBES 5 AND 6

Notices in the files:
firmware/dekatron-bringup/src/main.cpp:
SPDX-License-Identifier: MIT
